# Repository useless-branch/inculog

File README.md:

# inculog
Raspberry Pi Software to connect to an incubator device through RS232 and to an external sensor PCB via CAN.
All data measured by the sensors in the incubator and the external PCB are collected and transmitted
to an influxDB database.
## Press Reference
See the press release of this projet at: [Pforzheim University](https://www.hs-pforzheim.de/en/news_detailansicht/news/masterstudiengang_embedded_systems_student_optimiert_inkubator_im_labor)

# Compiling the Software
## Building for PC
To build the software for your PC just use the CMake-File and your favorite build environment:
```commandline
mkdir build
cd build
cmake .. -DCMAKE_C_COMPILER=clang -DCMAKE_CXX_COMPILER=clang++ -G "Ninja"
ninja
```

## Crosscompile for the Raspi on PC
If you want to compile the project directly on the Raspi just skip this step and use the method from above!

To use cross compilation install all needed dependencies on the Raspberry Pi:
- Base-devel / build-essentials
- fmt
- clang
- ninja

Copy the whole root folder of the raspberry pi onto `~/sysroot`.

Change the sysroot path in the cmake call to your local sysroot path (needs to be absolute!) and then run:
```commandline
mkdir build_pi
cd build_pi
cmake .. -DCMAKE_C_COMPILER=clang -DCMAKE_CXX_COMPILER=clang++ -DCMAKE_TOOLCHAIN_FILE=../toolchain-rpi.cmake -DCMAKE_SYSROOT=/home/<USERNAME>/sysroot -G "Ninja"
```

# Raspberry Pi Setup
## Installing Linux and kernel update
On the *Raspberry Pi Zero 2 W* is running aarch64 Linux with the raspi kernel.
Just install aarch64 as described in the Archlinuxarm-Wiki. Note: Use the 64-Bit kernel!
https://archlinuxarm.org/platforms/armv8/broadcom/raspberry-pi-zero-2

After that you can boot your pi and update the kernel to the raspi kernel with pacman.
```commandline
pacman -Syyu
```

## Enable UART and CAN
Update the following files `/boot/config.txt` to
```text
# See /boot/overlays/README for all available options
dtoverlay=vc4-kms-v3d
dtoverlay=disable_bt
initramfs initramfs-linux.img followkernel

[pi4]
# Run as fast as firmware / board allows
arm_boost=1

[all]
enable_uart=1
dtparam=spi=on
dtoverlay=mcp251xfd,spi0-0,oscillator=40000000,interrupt=25
```
and the file `/boot/cmdline.txt` to
```text
root=/dev/mmcblk0p2 rw rootwait console=tty1 selinux=0 plymouth.enable=0 smsc95xx.turbo_mode=N dwc_otg.lpm_enable=0
```
*Reboot!*

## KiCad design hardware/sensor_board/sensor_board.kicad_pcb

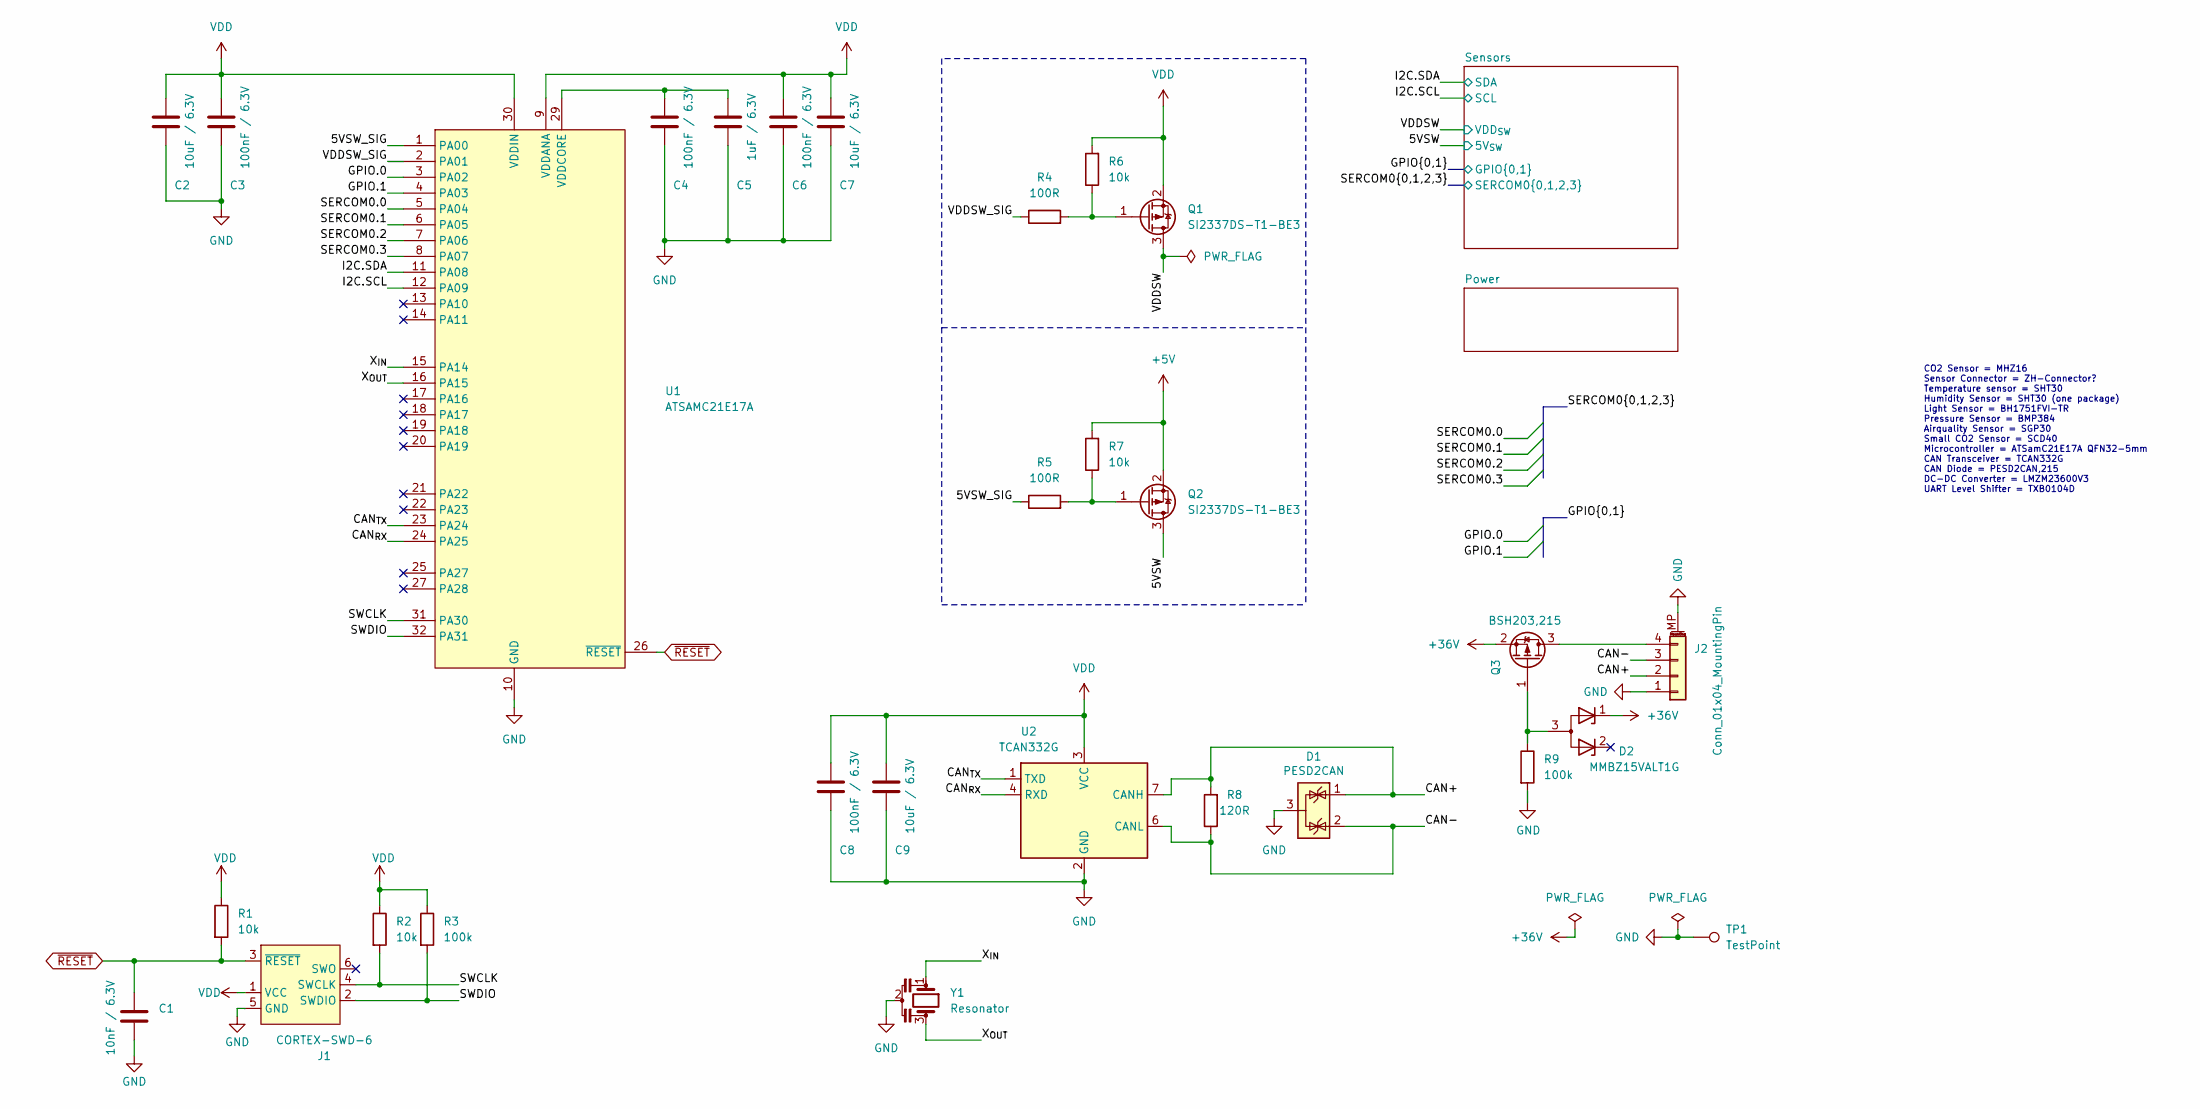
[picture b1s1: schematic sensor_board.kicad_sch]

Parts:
C1: 10nF / 6.3V; C_0402_1005Metric; MOUSER_NO 81-GRM155R71H103KA8D
C2, C7, C9: 10uF / 6.3V; C_0603_1608Metric; MOUSER_NO 81-GRM188R60J106ME4D
C3, C4, C6, C8: 100nF / 6.3V; C_0402_1005Metric; MOUSER_NO 81-GCJ188R71H104KA2D
C5: 1uF / 6.3V; C_0603_1608Metric; MOUSER_NO 81-LLR185C70G105ME3L
D1: PESD2CAN; SOT-23; MOUSER_NO 771-PESD2CAN-T/R
D2: MMBZ15VALT1G; SOT-23; MOUSER_NO 863-SZMMBZ15VALT1G
J1: CORTEX-SWD-6; Tag-Connect_TC2030-IDC-NL_2x03_P1.27mm_Vertical; MOUSER_NO DO NOT ORDER
J2: Conn_01x04_MountingPin; Molex_CLIK-Mate_502382-0470_1x04-1MP_P1.25mm_Vertical; Farnell_NO 9733060
Q1, Q2: SI2337DS-T1-BE3; SOT-23; MOUSER_NO 78-SI2337DS-T1-BE3
Q3: BSH203,215; SOT-23; MOUSER_NO 771-BSH203215
R1, R2, R6, R7: 10k; R_0402_1005Metric; MOUSER_NO DO NOT ORDER
R3, R9: 100k; R_0402_1005Metric; MOUSER_NO DO NOT ORDER
R4, R5: 100R; R_0402_1005Metric; MOUSER_NO DO NOT ORDER
R8: 120R; R_1206_3216Metric; MOUSER_NO DO NOT ORDER
TP1: TestPoint; TestPoint_Keystone_5015_Micro-Minature; MOUSER_NO 534-5015
U1: ATSAMC21E17A; QFN-32-1EP_5x5mm_P0.5mm_EP3.6x3.6mm; MOUSER_NO DO NOT ORDER
U2: TCAN332G; SOIC-8_3.9x4.9mm_P1.27mm; MOUSER_NO DO NOT ORDER
Y1: Resonator; Resonator_SMD_Murata_CSTxExxV-3Pin_3.0x1.1mm; MOUSER_NO DO NOT ORDER

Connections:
+5V: Q2.2 (S), R7.2; also elsewhere on the board
+36V: D2.1 (K), Q3.2 (S); also elsewhere on the board
/5VSW: Q2.3 (D); also elsewhere on the board
/5VSW_SIG: R5.1, U1.1 (PA00)
/CAN+: D1.1 (K), J2.2, R8.2, U2.7 (CANH)
/CAN-: D1.2 (K), J2.3, R8.1, U2.6 (CANL)
/CAN_{RX}: U1.24 (PA25), U2.4 (RXD)
/CAN_{TX}: U1.23 (PA24), U2.1 (TXD)
/GPIO.0: U1.3 (PA02); also elsewhere on the board
/GPIO.1: U1.4 (PA03); also elsewhere on the board
/I2C.SCL: U1.12 (PA09); also elsewhere on the board
/I2C.SDA: U1.11 (PA08); also elsewhere on the board
/SERCOM0.0: U1.5 (PA04); also elsewhere on the board
/SERCOM0.1: U1.6 (PA05); also elsewhere on the board
/SERCOM0.2: U1.7 (PA06); also elsewhere on the board
/SERCOM0.3: U1.8 (PA07); also elsewhere on the board
/SWCLK: J1.4 (SWCLK), R2.2, U1.31 (PA30)
/SWDIO: J1.2 (SWDIO), R3.2, U1.32 (PA31)
/VDDSW: Q1.3 (D); also elsewhere on the board
/VDDSW_SIG: R4.1, U1.2 (PA01)
/X_{IN}: U1.15 (PA14), Y1.1
/X_{OUT}: U1.16 (PA15), Y1.3
GND: C1.1, C2.2, C3.2, C4.2, C5.2, C6.2, C7.2, C8.2, C9.2, D1.3 (A), J1.5 (GND), J2.1, J2.MP (MountPin), R9.2, TP1.1, U1.10 (GND), U1.28 (GND), U2.2 (GND), Y1.2; also elsewhere on the board
unnamed: C4.1, C5.1, U1.29 (VDDCORE)
unnamed: D2.3 (A), Q3.1 (G), R9.1
unnamed: J2.4, Q3.3 (D)
unnamed: Q1.1 (G), R4.2, R6.1
unnamed: Q2.1 (G), R5.2, R7.1
VDD: C2.1, C3.1, C6.1, C7.1, C8.1, C9.1, J1.1 (VCC), Q1.2 (S), R1.1, R2.1, R3.1, R6.2, U1.9 (VDDANA), U1.30 (VDDIN), U2.3 (VCC); also elsewhere on the board
~RESET: C1.2, J1.3 (~RESET), R1.2, U1.26 (~RESET)

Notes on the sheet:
CO2 Sensor = MHZ16 Sensor Connector = ZH-Connector? Temperature sensor = SHT30 Humidity Sensor = SHT30 (one package) Light Sensor = BH1751FVI-TR Pressure Sensor = BMP384 Airquality Sensor = SGP30 Small CO2 Sensor = SCD40 Microcontroller = ATSamC21E17A QFN32-5mm CAN Transceiver = TCAN332G CAN Diode 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

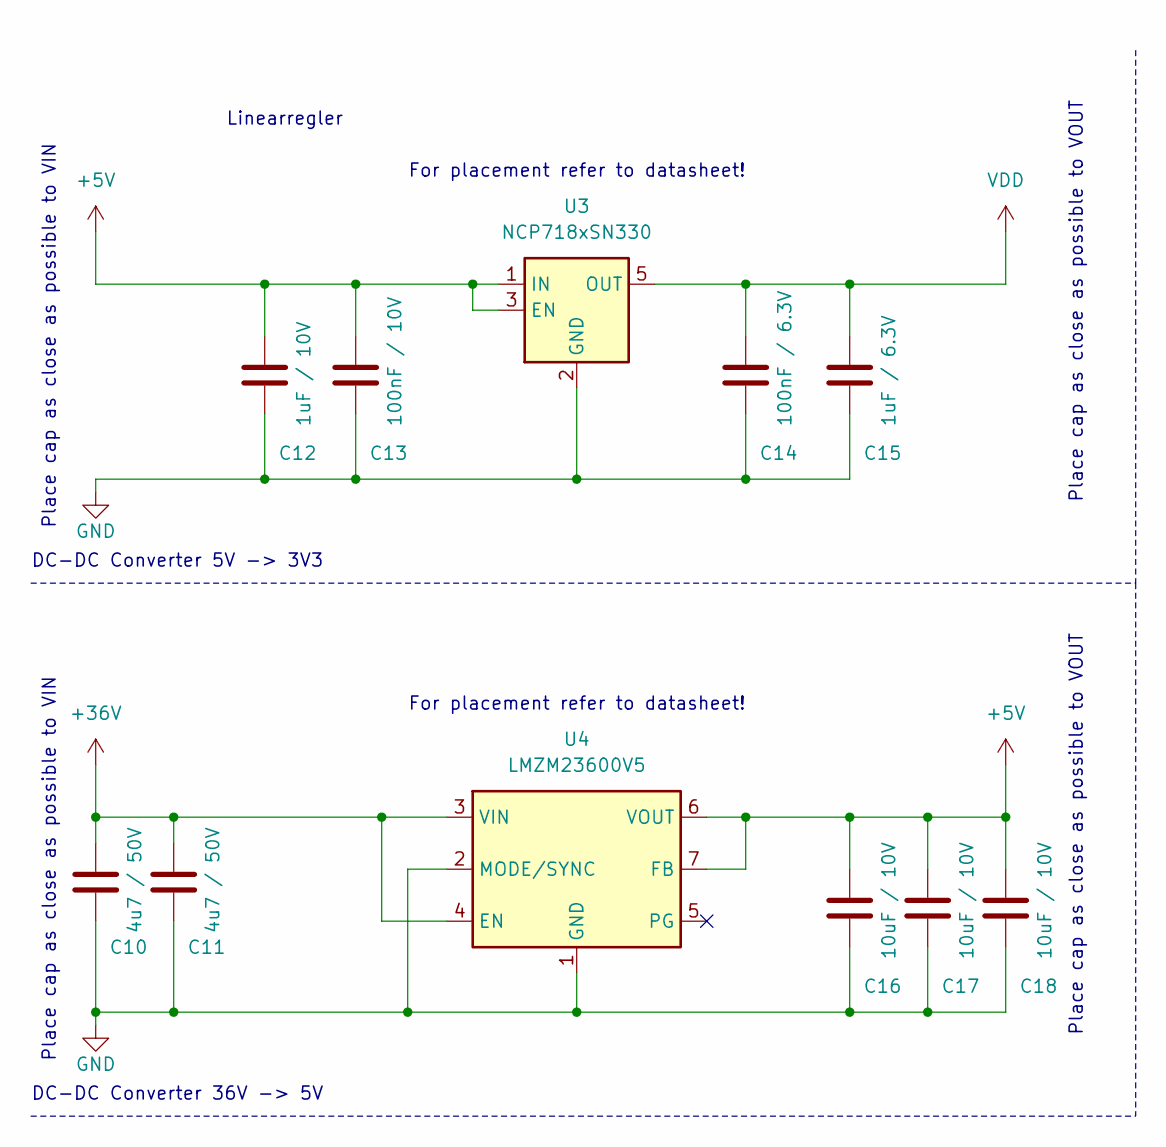
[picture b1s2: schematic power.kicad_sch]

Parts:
C10, C11: 4u7 / 50V; C_0805_2012Metric; MOUSER_NO 81-GRT21BC71H475KE3L
C12: 1uF / 10V; C_0603_1608Metric; MOUSER_NO 81-GRM18R61A105KA61J
C13: 100nF / 10V; C_0402_1005Metric; MOUSER_NO 81-GRM18R61A105KA61J
C14: 100nF / 6.3V; C_0402_1005Metric; MOUSER_NO 81-GRM18R61A105KA61J
C15: 1uF / 6.3V; C_0603_1608Metric; MOUSER_NO 81-LLR185C70G105ME3L
C16, C17, C18: 10uF / 10V; C_0603_1608Metric; MOUSER_NO 81-GRT188C81A106ME3D
U3: NCP718xSN330; SOT-23-5; MOUSER_NO 863-NCP718ASN330T1G
U4: LMZM23600V5; Texas_SIL0010A_MicroSiP-10-1EP_3.8x3mm_P0.6mm_EP0.7x2.9mm_T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; MOUSER_NO DO NOT ORDER

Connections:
+5V: C12.1, C13.1, C16.1, C17.1, C18.1, U3.1 (IN), U3.3 (EN), U4.6 (VOUT), U4.7 (FB); also elsewhere on the board
+36V: C10.1, C11.1, U4.3 (VIN), U4.4 (EN); also elsewhere on the board
GND: C10.2, C11.2, C12.2, C13.2, C14.2, C15.2, C16.2, C17.2, C18.2, U3.2 (GND), U4.1 (GND), U4.2 (MODE/SYNC), U4.11 (GND); also elsewhere on the board
VDD: C14.1, C15.1, U3.5 (OUT); also elsewhere on the board

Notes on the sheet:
DC-DC Converter 36V -> 5V
For placement refer to datasheet!
DC-DC Converter 5V -> 3V3
Linearregler
Place cap as close as possible to VOUT
Place cap as close as possible to VIN

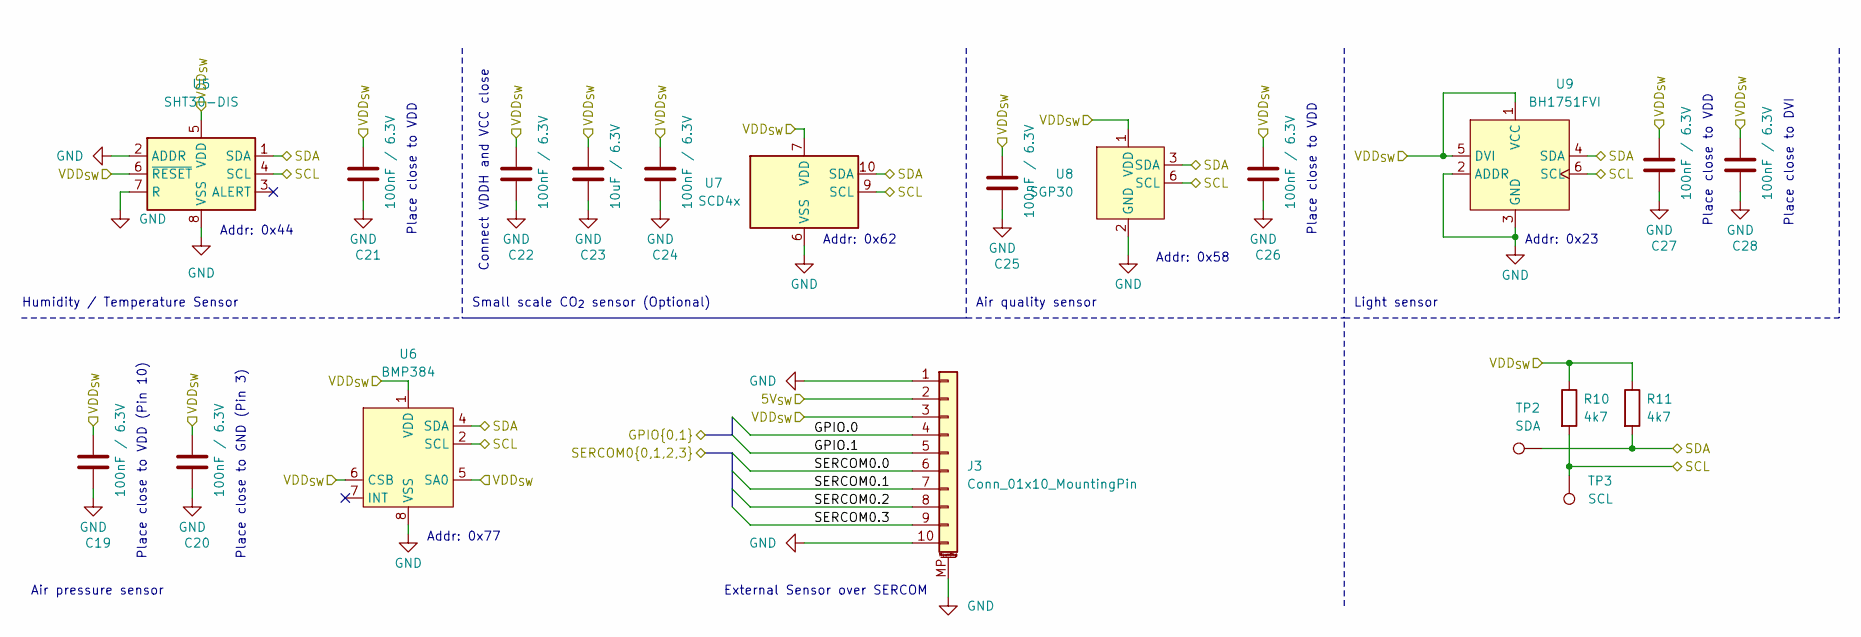
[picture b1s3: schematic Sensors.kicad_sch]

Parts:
C19, C20, C21, C22, C24, C25, C26, C27, C28: 100nF / 6.3V; C_0402_1005Metric; MOUSER_NO 81-GCJ188R71H104KA2D
C23: 10uF / 6.3V; C_0603_1608Metric; MOUSER_NO 81-GRM188R60J106ME4D
J3: Conn_01x10_MountingPin; Molex_PicoBlade_53261-1071_1x10-1MP_P1.25mm_Horizontal; MOUSER_NO 538-53261-1071
R10, R11: 4k7; R_0402_1005Metric; MOUSER_NO DO NOT ORDER
TP2: SDA; TestPoint_Pad_D1.0mm; MOUSER_NO DO NOT ORDER
TP3: SCL; TestPoint_Pad_D1.0mm; MOUSER_NO DO NOT ORDER
U5: SHT30-DIS; Sensirion_DFN-8-1EP_2.5x2.5mm_P0.5mm_EP1.1x1.7mm; MOUSER_NO 403-SHT30-DIS-F
U6: BMP384; MOUSER_NO 262-BMP384
U7: SCD4x; MOUSER_NO DO NOT ORDER
U8: SGP30; DFN-6-P0.8mm_EP1.25x1.7mm; MOUSER_NO 403-SGP30-2.5K
U9: BH1751FVI; WSOF6; MOUSER_NO 755-BH1751FVI-TR

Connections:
/5VSW: J3.2; also elsewhere on the board
/GPIO.0: J3.4; also elsewhere on the board
/GPIO.1: J3.5; also elsewhere on the board
/I2C.SCL: R10.2, TP3.1, U5.4 (SCL), U6.2 (SCL), U7.9 (SCL), U8.6 (SCL), U9.6 (SCL); also elsewhere on the board
/I2C.SDA: R11.2, TP2.1, U5.1 (SDA), U6.4 (SDA), U7.10 (SDA), U8.3 (SDA), U9.4 (SDA); also elsewhere on the board
/SERCOM0.0: J3.6; also elsewhere on the board
/SERCOM0.1: J3.7; also elsewhere on the board
/SERCOM0.2: J3.8; also elsewhere on the board
/SERCOM0.3: J3.9; also elsewhere on the board
/VDDSW: C19.1, C20.1, C21.1, C22.1, C23.1, C24.1, C25.1, C26.1, C27.1, C28.1, J3.3, R10.1, R11.1, U5.5 (VDD), U5.6 (~RESET), U6.1 (VDD), U6.5 (SA0), U6.6 (CSB), U6.10 (VDD), U7.7 (VDD), U7.19 (VDD), U8.1 (VDD), U8.5 (VDDH), U9.1 (VCC), U9.5 (DVI); also elsewhere on the board
GND: C19.2, C20.2, C21.2, C22.2, C23.2, C24.2, C25.2, C26.2, C27.2, C28.2, J3.1, J3.10, J3.MP (MountPin), U5.2 (ADDR), U5.7 (R), U5.8 (VSS), U5.9 (VSS), U6.3 (VSS), U6.8 (VSS), U6.9 (VSS), U7.6 (VSS), U7.20 (VSS), U7.21 (VSS), U8.2 (GND), U8.4 (R), U8.7 (EP), U9.2 (ADDR), U9.3 (GND); also elsewhere on the board

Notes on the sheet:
Connect VDDH and VCC close
Addr: 0x23
Addr: 0x77
Place close to GND (Pin 3)
Place close to VDD (Pin 10)
External Sensor over SERCOM
Place close to VDD
Addr: 0x44
Air pressure sensor
Air quality sensor
Place close to DVI
Addr: 0x58
Small scale CO_{2} sensor (Optional)
Light sensor
Humidity / Temperature Sensor
Addr: 0x62

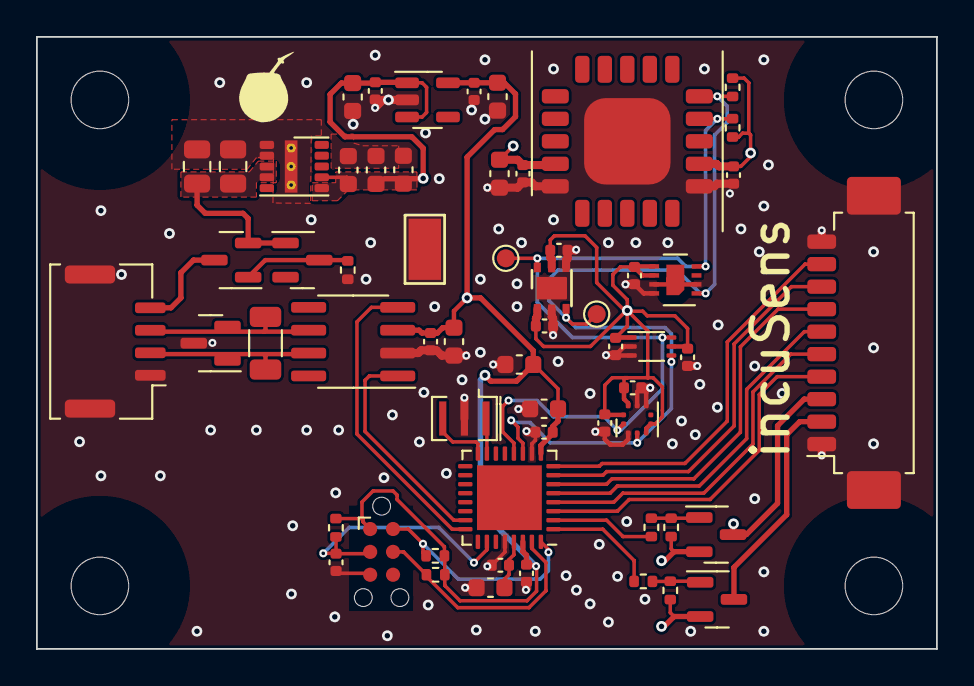
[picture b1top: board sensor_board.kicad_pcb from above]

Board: 4 copper layers, 50.0 x 34.0 mm, 64 parts (0 on the bottom side), 30 nets.

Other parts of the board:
Hole1, Hole2, Hole3, Hole4: MountingHole_3.2mm_M3_no_Mask

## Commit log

2021-09-07 added some early presentation
2021-09-29 added poster file
2021-09-29 changed poster file
2021-10-13 updated schematics
2021-10-14 all bricked...
2021-10-15 removed backup
2021-10-15 solved issues with ERC
2021-10-15 removed backups
2021-10-15 changed gitignore to discard kicad backups
2021-10-19 did some stuff
2021-10-29 added gitignore
2021-10-29 removed build files
2021-10-29 updated main
2021-10-29 moved own classes to new files
2021-11-05 finished schematic and added board
2021-11-06 review
2021-11-08 updated pcb
2021-11-08 zeug!
2021-11-08 gitignore
2021-11-15 finished board
2021-11-15 researched parts
2021-11-16 updated after meeting
2021-11-17 updated board with new connector
2021-11-17 changed to tag connect due to chip shortage
2021-11-18 some stuff!
2021-11-19 moved hardware to new repository
2021-12-08 added output file
2021-12-08 traced output of incubator
2021-12-09 changed some stuff
2021-12-09 removed extensions in cmakeslists
2021-12-12 changed bit to memcpy
2021-12-14 updated to RaspberryPI-GPIO
2021-12-15 added flush in send funcion
2021-12-15 changed send bytes from 6 to 5
2021-12-29 reorganized project repository
2021-12-29 changed target name in CMakeLists
2022-01-18 before testing
2022-01-18 removed idea and added to gitignore
2022-03-15 updated Inculog software for two boards
2022-06-20 cleaned up git
2022-12-30 Update README.md
    added press references
